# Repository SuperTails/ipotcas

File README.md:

**IP over Tin Can and String** (IPoTCaS, pronounced "eye-poh-tee-kass"),
also known as EtherKnit or "what is this annoying buzzing noise",
is a revolutionary new way to connect to the internet over a fiber connection.

Using only two pieces of string and lots of annoying sounds,
IPoTCaS can create a **6.9 kbps** connection capable of browsing the web,
downloading files, and giving you a newfound distaste for web bloat.

# Physical Setup

The linear rails are sourced from two listings on Amazon,
but I'd highly recommend just using the first one because the wider rails are much worse
(though the CAD will require some modification):
- [Small rails](https://www.amazon.com/dp/B0D54LDBHN?ref=ppx_yo2ov_dt_b_fed_asin_title)
- [Large rails](https://www.amazon.com/dp/B088B6XN2J?ref=ppx_yo2ov_dt_b_fed_asin_title&th=1)

Any generic Kevlar kite string will probably work,
but I used specifically
[this amazon listing](https://www.amazon.com/dp/B088PT4KKG?ref=ppx_yo2ov_dt_b_fed_asin_title&th=1)
from `emma kites`.

The mount CAD is available on
[Onshape](https://cad.onshape.com/documents/322e68c2d75961563174bd8a/w/bb42fd02dcb60f17fdcb0973/e/e357883cf5ed7cb39072be44?renderMode=0&uiState=687ea4469b7eec1ebb9bbd03).
I have not tested with materials other than PLA.
The model is designed to work with metric heat-set inserts to hold down the rails.

# Modulation

IPoTCaS uses 32-QAM and 12-carrier OFDM between 7 and 14 kHz.

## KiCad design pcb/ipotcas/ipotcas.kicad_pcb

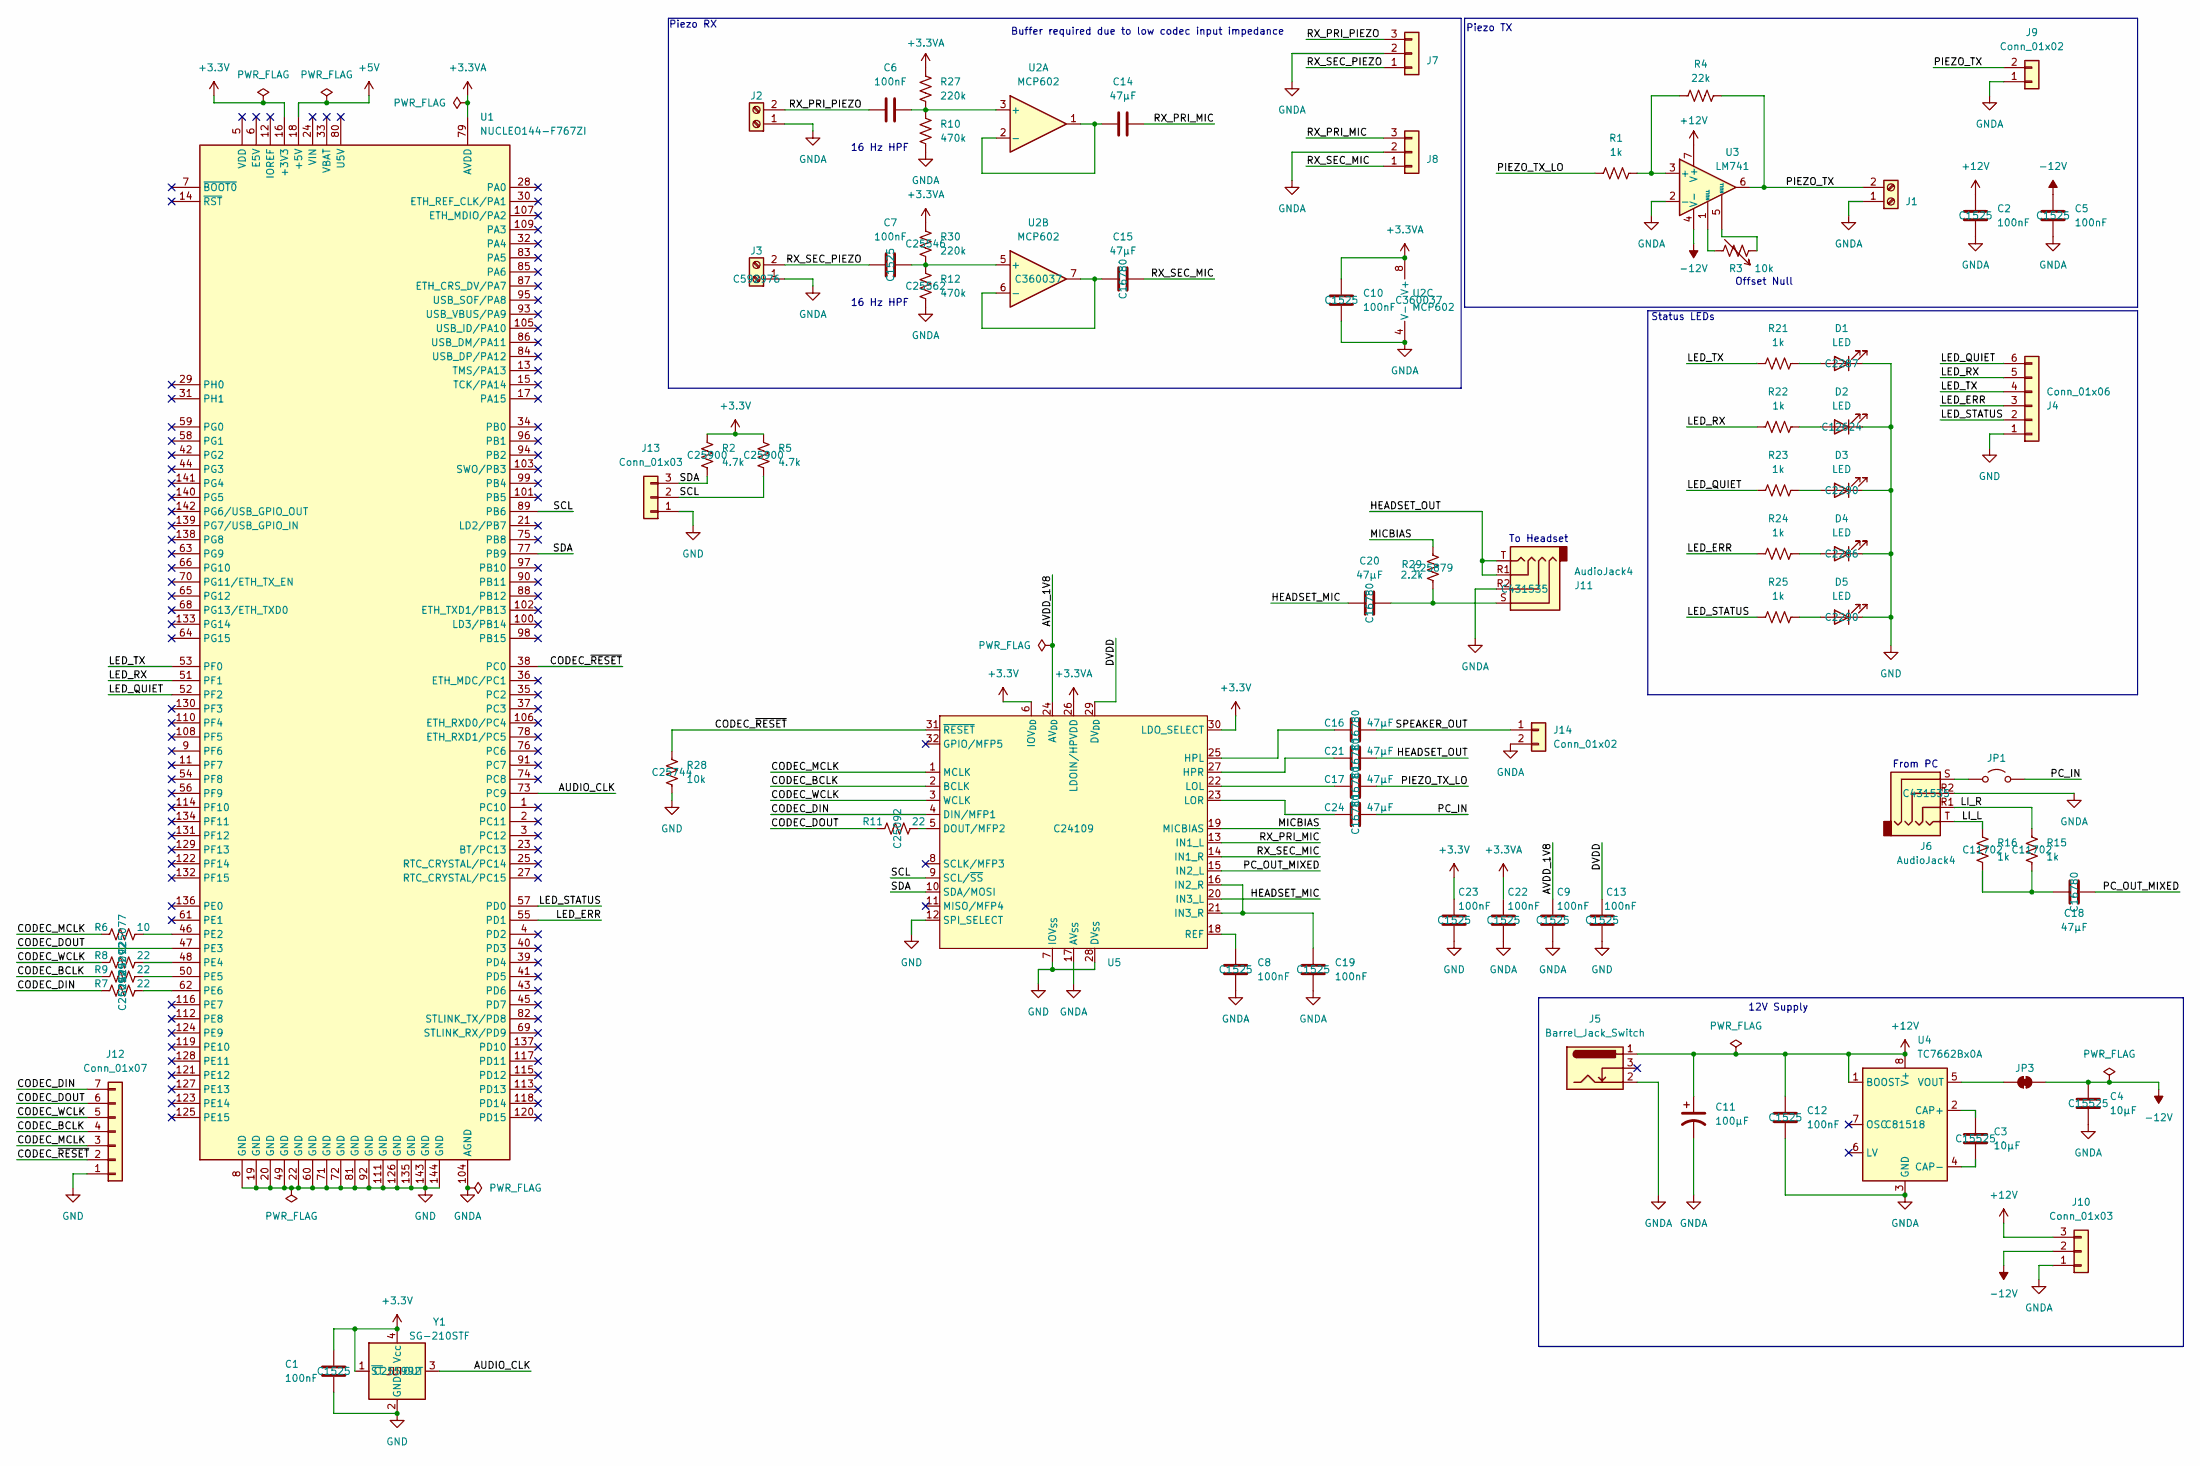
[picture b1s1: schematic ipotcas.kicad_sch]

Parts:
C1, C2, C5, C8, C9, C10, C12, C13, C19, C22, C23: 100nF; C_0402_1005Metric; JLC P/N C1525
C3, C4: 10µF; C_0402_1005Metric; JLC P/N C15525
C6, C7: 100nF; C_0402_1005Metric_Pad0.74x0.62mm_HandSolder; JLC P/N C1525
C11: 100µF; CP_Radial_D5.0mm_P2.50mm
C14, C15, C16, C17, C18, C20, C24: 47µF; C_0805_2012Metric; JLC P/N C16780
C21: 47µF; C_0603_1608Metric_Pad1.08x0.95mm_HandSolder; JLC P/N C16780
D1: LED; LED_0805_2012Metric_Pad1.15x1.40mm_HandSolder; JLC P/N C2287
D2: LED; LED_0805_2012Metric_Pad1.15x1.40mm_HandSolder; JLC P/N C12624
D3, D5: LED; LED_0805_2012Metric_Pad1.15x1.40mm_HandSolder; JLC P/N C2290
D4: LED; LED_0805_2012Metric_Pad1.15x1.40mm_HandSolder; JLC P/N C2286
J1, J2, J3: Screw_Terminal_01x02; TE_282837-2; JLC P/N C592976
J4: Conn_01x06; PinHeader_1x06_P2.54mm_Vertical
J5: Barrel_Jack_Switch; CUI_PJ-002B
J6, J11: AudioJack4; Jack_3.5mm_PJ320D_Horizontal; JLC P/N C431535
J7, J8, J10, J13: Conn_01x03; PinHeader_1x03_P2.54mm_Vertical
J9: Conn_01x02; PinHeader_1x02_P2.54mm_Vertical
J12: Conn_01x07; PinHeader_1x07_P2.54mm_Vertical
J14: Conn_01x02; PinSocket_1x02_P2.54mm_Vertical
JP1: Jumper_2_Open; PinHeader_1x02_P2.54mm_Vertical
JP3: SolderJumper_2_Bridged; SolderJumper-2_P1.3mm_Bridged_RoundedPad1.0x1.5mm
R1: 1k; R_0402_1005Metric_Pad0.72x0.64mm_HandSolder; JLC P/N C11702
R2, R5: 4.7k; R_0402_1005Metric; JLC P/N C25900
R3: 10k; Potentiometer_Bourns_3296W_Vertical; JLC P/N C118954
R4: 22k; R_0402_1005Metric_Pad0.72x0.64mm_HandSolder; JLC P/N C25768
R6: 10; R_0402_1005Metric; JLC P/N C25077
R7, R8, R9, R11: 22; R_0402_1005Metric; JLC P/N C25092
R10, R12: 470k; R_0402_1005Metric_Pad0.72x0.64mm_HandSolder; JLC P/N C25562
R15, R16: 1k; R_0402_1005Metric; JLC P/N C11702
R21, R22, R23, R24, R25: 1k; R_0805_2012Metric_Pad1.20x1.40mm_HandSolder
R27, R30: 220k; R_0402_1005Metric_Pad0.72x0.64mm_HandSolder; JLC P/N C25546
R28: 10k; R_0402_1005Metric; JLC P/N C25744
R29: 2.2k; R_0402_1005Metric; JLC P/N C25879
U1: NUCLEO144-F767ZI; ST_Morpho_Connector_144_STLink
U2: MCP602; SOIC-8_3.9x4.9mm_P1.27mm; JLC P/N C360037
U3: LM741; SOP-8_3.9x4.9mm_P1.27mm; JLC P/N C5145278
U4: TC7662Bx0A; SOIC-8_3.9x4.9mm_P1.27mm; JLC P/N C81518
U5: QFN-32-1EP_5x5mm_P0.5mm_EP3.45x3.45mm_ThermalVias; JLC P/N C24109
Y1: SG-210STF; Oscillator_SMD_SeikoEpson_SG210-4Pin_2.5x2.0mm; JLC P/N C255992

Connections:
+3.3V: C1.1, C23.1, R2.1, R5.1, U1.16 (+3V3), U5.6 (IOV_{DD}), U5.30 (LDO_SELECT), Y1.1 (~ST), Y1.4 (Vcc)
+3.3VA: C10.1, C22.1, R27.1, R30.1, U1.79 (AVDD), U2.8 (V+), U5.26 (LDOIN/HPVDD)
+5V: U1.18 (+5V)
+12V: C2.1, C11.1, C12.1, J5.1, J10.3, U3.7 (V+), U4.1 (BOOST), U4.8 (V+)
-12V: C4.1, C5.1, J10.2, JP3.2 (B), U3.4 (V-)
/AUDIO_CLK: U1.73 (PC9), Y1.3 (OUT)
/AVDD_1V8: C9.1, U5.24 (AV_{DD})
/CODEC_BCLK: J12.4, R9.1, U5.2 (BCLK)
/CODEC_DIN: J12.7, R7.1, U5.4 (DIN/MFP1)
/CODEC_DOUT: J12.6, R11.1, U1.47 (PE3)
/CODEC_MCLK: J12.3, R6.1, U5.1 (MCLK)
/CODEC_WCLK: J12.5, R8.1, U5.3 (WCLK)
/CODEC_~RESET: J12.2, R28.1, U1.38 (PC0), U5.31 (~RESET)
/DVDD: C13.1, U5.29 (DV_{DD})
/HEADSET_MIC: C20.1, U5.20 (IN3_L)
/HEADSET_OUT: C21.2, J11.R1, J11.T
/LED_ERR: J4.3, R24.1, U1.55 (PD1)
/LED_QUIET: J4.6, R23.1, U1.52 (PF2)
/LED_RX: J4.5, R22.1, U1.51 (PF1)
/LED_STATUS: J4.2, R25.1, U1.57 (PD0)
/LED_TX: J4.4, R21.1, U1.53 (PF0)
/LI_L: J6.T, R16.1
/LI_R: J6.R1, R15.1
/MICBIAS: R29.2, U5.19 (MICBIAS)
/PC_IN: C24.2, JP1.2 (B)
/PC_OUT_MIXED: C18.2, U5.15 (IN2_L)
/PIEZO_TX: J1.2, J9.2, R4.2, U3.6
/PIEZO_TX_LO: C17.2, R1.1
/RX_PRI_MIC: C14.2, J8.3, U5.13 (IN1_L)
/RX_PRI_PIEZO: C6.1, J2.2, J7.3
/RX_SEC_MIC: C15.2, J8.1, U5.14 (IN1_R)
/RX_SEC_PIEZO: C7.1, J3.2, J7.1
/SCL: J13.2, R5.2, U1.89 (PB6), U5.9 (SCL/~SS)
/SDA: J13.3, R2.2, U1.77 (PB9), U5.10 (SDA/MOSI)
/SPEAKER_OUT: C16.2, J14.1
GND: C1.2, C13.2, C23.2, D1.1 (K), D2.1 (K), D3.1 (K), D4.1 (K), D5.1 (K), J4.1, J12.1, J13.1, R28.2, U1.8 (GND), U1.19 (GND), U1.20 (GND), U1.22 (GND), U1.49 (GND), U1.60 (GND), U1.71 (GND), U1.72 (GND), U1.81 (GND), U1.92 (GND), U1.111 (GND), U1.126 (GND), U1.135 (GND), U1.143 (GND), U1.144 (GND), U5.7 (IOV_{SS}), U5.12 (SPI_SELECT), U5.28 (DV_{SS}), Y1.2 (GND)
GNDA: C2.2, C4.2, C5.2, C8.2, C9.2, C10.2, C11.2, C12.2, C19.2, C22.2, J1.1, J2.1, J3.1, J5.2, J6.R2, J7.2, J8.2, J9.1, J10.1, J11.R2, J14.2, R10.2, R12.2, U1.104 (AGND), U2.4 (V-), U3.2 (-), U4.3 (GND), U5.17 (AV_{SS})
unnamed: C18.1, R15.2, R16.2
unnamed: C20.2, J11.S, R29.1
unnamed: D1.2 (A), R21.2
unnamed: D2.2 (A), R22.2
unnamed: D3.2 (A), R23.2
unnamed: D4.2 (A), R24.2
unnamed: D5.2 (A), R25.2
unnamed: J6.S, JP1.1 (A)
unnamed: JP3.1 (A), U4.5 (VOUT)
unnamed: R3.1, U3.5 (NULL)
unnamed: R3.2, U3.1 (NULL)
unnamed: R6.2, U1.46 (PE2)
unnamed: R8.2, U1.48 (PE4)
unnamed: R9.2, U1.50 (PE5)
unnamed: R7.2, U1.62 (PE6)
unnamed: C6.2, R10.1, R27.2, U2.3 (+)
unnamed: C14.1, U2.1, U2.2 (-)
unnamed: C7.2, R12.1, R30.2, U2.5 (+)
unnamed: C15.1, U2.6 (-), U2.7
unnamed: R1.2, R4.1, U3.3 (+)
unnamed: C3.1, U4.2 (CAP+)
unnamed: C3.2, U4.4 (CAP-)
unnamed: R11.2, U5.5 (DOUT/MFP2)
unnamed: C16.1, U5.25 (HPL)
unnamed: C21.1, U5.27 (HPR)
unnamed: C19.1, U5.16 (IN2_R), U5.21 (IN3_R)
unnamed: C17.1, U5.22 (LOL)
unnamed: C24.1, U5.23 (LOR)
unnamed: C8.1, U5.18 (REF)

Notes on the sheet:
16 Hz HPF
To Headset
Piezo TX
Buffer required due to low codec input impedance
Piezo RX
12V Supply
Status LEDs
Offset Null
From PC

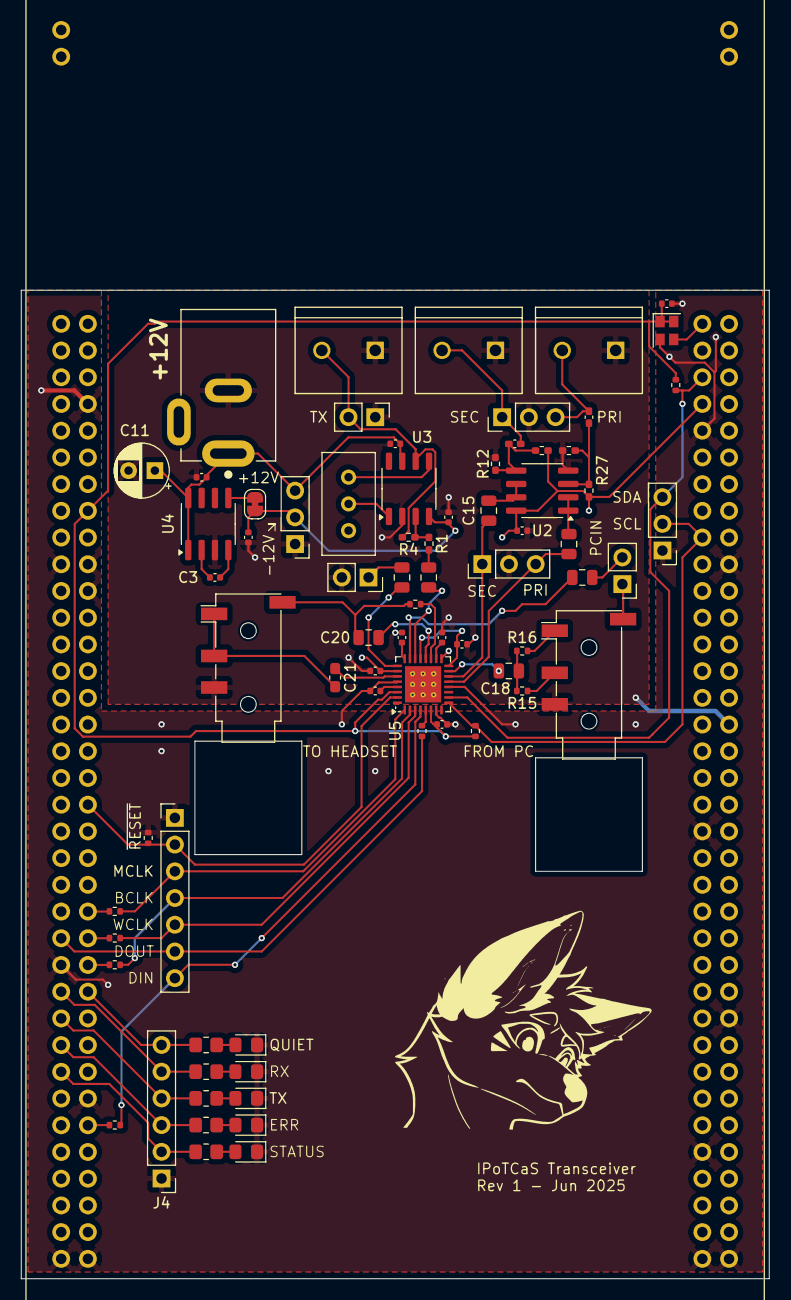
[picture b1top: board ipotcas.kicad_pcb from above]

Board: 4 copper layers, 71.1 x 94.0 mm, 74 parts (0 on the bottom side), 65 nets.

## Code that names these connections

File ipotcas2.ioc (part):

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Mcu.Name=STM32F767ZITx
Mcu.Package=LQFP144
Mcu.UserName=STM32F767ZITx
PA0/WKUP.Signal=ADCx_IN0
PA1.GPIOParameters=GPIO_Label
PA1.GPIO_Label=RMII_REF_CLK [LAN8742A-CZ-TR_REFCLK0]
PA1.Mode=RMII
PA1.Signal=ETH_REF_CLK
PA10.GPIOParameters=GPIO_Label
PA10.GPIO_Label=USB_ID
PA10.Signal=USB_OTG_FS_ID
PA11.GPIOParameters=GPIO_Speed,GPIO_PuPd,GPIO_Mode
PA11.GPIO_Mode=GPIO_MODE_AF_PP
PA11.GPIO_PuPd=GPIO_NOPULL
PA11.GPIO_Speed=GPIO_SPEED_FREQ_VERY_HIGH
PA11.Mode=Device_Only
PA11.Signal=USB_OTG_FS_DM
PA12.GPIOParameters=GPIO_Speed,GPIO_PuPd,GPIO_Mode
PA12.GPIO_Mode=GPIO_MODE_AF_PP
PA12.GPIO_PuPd=GPIO_NOPULL
PA12.GPIO_Speed=GPIO_SPEED_FREQ_VERY_HIGH
PA12.Mode=Device_Only
PA12.Signal=USB_OTG_FS_DP
PA13.GPIOParameters=GPIO_Label
PA13.GPIO_Label=TMS
PA13.Mode=Serial_Wire
PA13.Signal=SYS_JTMS-SWDIO
PA14.GPIOParameters=GPIO_Label
PA14.GPIO_Label=TCK
PA14.Mode=Serial_Wire
PA14.Signal=SYS_JTCK-SWCLK
PA2.GPIOParameters=GPIO_Label
PA2.GPIO_Label=RMII_MDIO [LAN8742A-CZ-TR_MDIO]
PA2.Mode=RMII
PA2.Signal=ETH_MDIO
PA3.Mode=Asynchronous
PA3.Signal=USART2_RX
PA4.Signal=COMP_DAC1_group
PA5.Signal=COMP_DAC2_group
PA7.GPIOParameters=GPIO_Label
PA7.GPIO_Label=RMII_CRS_DV [LAN8742A-CZ-TR_CRS_DV]
PA7.Mode=RMII
PA7.Signal=ETH_CRS_DV
PA8.GPIOParameters=GPIO_Label
PA8.GPIO_Label=USB_SOF [TP1]
PA8.Signal=USB_OTG_FS_SOF
PA9.GPIOParameters=GPIO_Label
PA9.GPIO_Label=USB_VBUS
PA9.Signal=USB_OTG_FS_VBUS
PB13.GPIOParameters=GPIO_Label
PB13.GPIO_Label=RMII_TXD1 [LAN8742A-CZ-TR_TXD1]
PB13.Mode=RMII
PB13.Signal=ETH_TXD1
PB3.GPIOParameters=GPIO_Label
PB3.GPIO_Label=SWO
PB3.Signal=SYS_JTDO-SWO
PB6.Mode=I2C
PB6.Signal=I2C1_SCL
PB7.GPIOParameters=GPIO_Label
PB7.GPIO_Label=LD2 [Blue]
PB7.Signal=GPIO_Output
PB9.Mode=I2C
PB9.Signal=I2C1_SDA
PC0.Signal=GPIO_Output
PC1.GPIOParameters=GPIO_Label
PC1.GPIO_Label=RMII_MDC [LAN8742A-CZ-TR_MDC]
PC1.Mode=RMII
PC1.Signal=ETH_MDC
PC13.GPIOParameters=GPIO_Label
PC13.GPIO_Label=USER_Btn [B1]
PC13.Signal=GPXTI13
PC14/OSC32_IN.Mode=LSE-External-Oscillator
PC14/OSC32_IN.Signal=RCC_OSC32_IN
PC15/OSC32_OUT.Mode=LSE-External-Oscillator
PC15/OSC32_OUT.Signal=RCC_OSC32_OUT
PC4.GPIOParameters=GPIO_Label
PC4.GPIO_Label=RMII_RXD0 [LAN8742A-CZ-TR_RXD0]
PC4.Mode=RMII
PC4.Signal=ETH_RXD0
PC5.GPIOParameters=GPIO_Label
PC5.GPIO_Label=RMII_RXD1 [LAN8742A-CZ-TR_RXD1]
PC5.Mode=RMII
PC5.Signal=ETH_RXD1
PC9.Mode=Audio_ClockIn
PC9.Signal=I2S_CKIN
PD0.GPIOParameters=GPIO_Label
PD0.GPIO_Label=LED_STATUS
PD0.Signal=GPIO_Output
PD1.GPIOParameters=GPIO_Label
PD1.GPIO_Label=LED_ERR
PD1.Signal=GPIO_Output
PD5.Mode=Asynchronous
PD5.Signal=USART2_TX
PD8.GPIOParameters=GPIO_Label
PD8.GPIO_Label=STLK_RX [STM32F103CBT6_PA3]
PD8.Mode=Asynchronous
PD8.Signal=USART3_TX
PD9.GPIOParameters=GPIO_Label
PD9.GPIO_Label=STLK_TX [STM32F103CBT6_PA2]
PD9.Mode=Asynchronous
PD9.Signal=USART3_RX
PE2.Mode=SAI_A_MasterWithClock
PE2.Signal=SAI1_MCLK_A
PE3.Mode=SAI_B_SyncSlave
PE3.Signal=SAI1_SD_B
PE4.Mode=SAI_A_MasterWithClock
PE4.Signal=SAI1_FS_A
PE5.Mode=SAI_A_MasterWithClock
PE5.Signal=SAI1_SCK_A
PE6.Mode=SAI_A_MasterWithClock
PE6.Signal=SAI1_SD_A
PF0.GPIOParameters=GPIO_Label
PF0.GPIO_Label=LED_TX
PF0.Signal=GPIO_Output
PF1.GPIOParameters=GPIO_Label
PF1.GPIO_Label=LED_RX
PF1.Signal=GPIO_Output
PF2.GPIOParameters=GPIO_Label
PF2.GPIO_Label=LED_QUIET
PF2.Signal=GPIO_Output
PG11.GPIOParameters=GPIO_Label
PG11.GPIO_Label=RMII_TX_EN [LAN8742A-CZ-TR_TXEN]
PG11.Mode=RMII
PG11.Signal=ETH_TX_EN
PG13.GPIOParameters=GPIO_Label
PG13.GPIO_Label=RMII_TXD0 [LAN8742A-CZ-TR_TXD0]
PG13.Mode=RMII
PG13.Signal=ETH_TXD0
PG6.GPIOParameters=GPIO_Label
PG6.GPIO_Label=USB_PowerSwitchOn [STMPS2151STR_EN]
PG6.Signal=GPIO_Output
PG7.GPIOParameters=GPIO_Label
PG7.GPIO_Label=USB_OverCurrent [STMPS2151STR_FAULT]
PG7.Signal=GPIO_Input
PH0/OSC_IN.GPIOParameters=GPIO_Label
PH0/OSC_IN.GPIO_Label=MCO [STM32F103CBT6_PA8]
PH0/OSC_IN.Mode=HSE-External-Clock-Source
PH0/OSC_IN.Signal=RCC_OSC_IN
PH1/OSC_OUT.Mode=HSE-External-Clock-Source
PH1/OSC_OUT.Signal=RCC_OSC_OUT
RCC.HSE_VALUE=8000000
RCC.SYSCLKFreq_VALUE=192000000
RCC.SYSCLKSource=RCC_SYSCLKSOURCE_PLLCLK
RCC.SYSCLKSourceVirtual=RCC_SYSCLKSOURCE_PLLCLK
board=NUCLEO-F767ZI
boardIOC=true

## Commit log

2025-05-02 Implement semi-working usb/ethernet bridge
2025-05-03 ip over uart :)
2025-05-03 Increased UART speed
2025-05-03 Functioning tx/rx
2025-05-04 OFDM and migrate to CubeMX
2025-05-04 Fix bugs and misc cleanup
2025-05-05 WORKING WITHOUT OFDM
2025-05-05 Working 3 OFDM
2025-05-06 Working 4.8 kbps
2025-05-06 Adjust sample time
2025-05-06 Adjust quiet detection
2025-05-13 Add more carriers; improve transmit speed
2025-05-14 WIP raised cosine filtering
2025-05-14 Use DMA for transmission
2025-05-14 Log DAC output to USB
2025-05-15 Add real time decoding and frequency switching
2025-05-20 Optimize transmission
2025-05-26 Optimize rx
2025-05-27 idk stuff but it kinda works
2025-05-28 Fix transmit underrun
2025-05-28 WIP frequency interleaving
2025-05-29 Add hamming code
2025-05-29 Compensate for phase drift
2025-05-29 Trim received packets
2025-05-30 it works
2025-05-30 Add transmit buffering
2025-06-07 Add PCB schematic rev1
2025-06-07 Fix silkscreen labeling
2025-06-07 Fix clearance violation
2025-06-16 Enable SAI and I2C1
2025-06-23 Port RX to new PCB
2025-06-24 Fix transmission
2025-06-25 Working 12 carrier pcb tx/rx
2025-06-29 Actually working
2025-07-14 aaaaaaaaaaaaaa
2025-07-14 Working 8-carrier visualizations
2025-07-15 Improve vis AGC
2025-07-18 Add readme
2025-07-21 Add all star button and fix AGC
2025-07-24 Add filtering, increase data rate, code cleanup, readme update
2025-07-24 Update plotting
2025-07-30 Add switch to demo ASK transmission
2025-07-30 Attempt to add audio streaming
2025-07-31 Add checksum; increase hamming code rate
2025-08-24 Add scrambler
2025-08-24 Add DMA for raw streaming
2025-08-30 Fix raw audio streaming maybe
